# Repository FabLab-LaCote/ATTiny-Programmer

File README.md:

#ATtiny Programmer

This shield for Arduino Nano is compatible for ATtiny 45, 85, 44 and 84

Find all informations here: http://www.fablab-lacote.ch/wiki/attiny

## Material
- 3x Resistors 220 ohms 0.25W
- 3x LEDS 3mm
- 1x capacitor 10uF
- 2x 15 pins header
- 1x IC chipset 8 pins

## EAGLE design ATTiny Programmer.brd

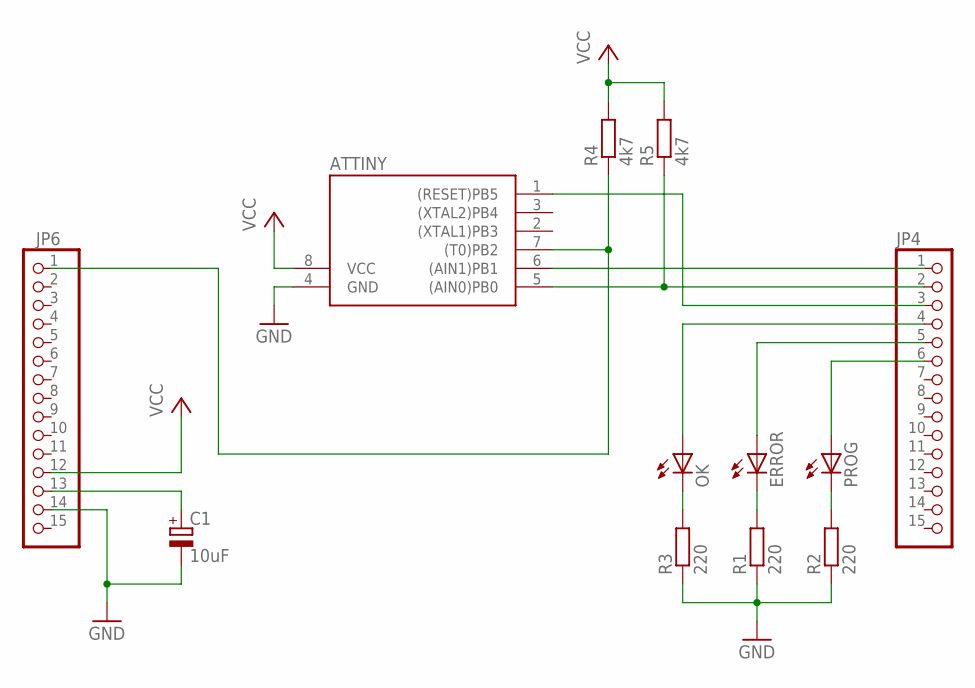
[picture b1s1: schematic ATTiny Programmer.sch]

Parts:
ATTINY: TINY10P; DIL08
C1: 10uF; E2-4
ERROR: Error; LED3MM
JP4: pinheader1; 1X15
JP6: pinheader2; 1X15
OK: Ok; LED3MM
PROG: Prog; LED3MM
R1, R2, R3: 220; 0207/7
R4, R5: 4k7; 0207/7

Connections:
GND: ATTINY.4 (GND), C1.-, JP6.14, R1.1, R2.1, R3.1
unnamed: OK.K (C), R3.2
unnamed: PROG.K (C), R2.2
unnamed: ERROR.K (C), R1.2
unnamed: C1.+, JP6.13
unnamed: JP4.4, OK.A
unnamed: ERROR.A, JP4.5
unnamed: ATTINY.1 ((RESET)PB5), JP4.3
unnamed: ATTINY.5 ((AIN0)PB0), JP4.2, R5.1
unnamed: ATTINY.6 ((AIN1)PB1), JP4.1
unnamed: ATTINY.7 ((T0)PB2), JP6.1, R4.1
unnamed: JP4.6, PROG.A
VCC: ATTINY.8 (VCC), JP6.12, R4.2, R5.2

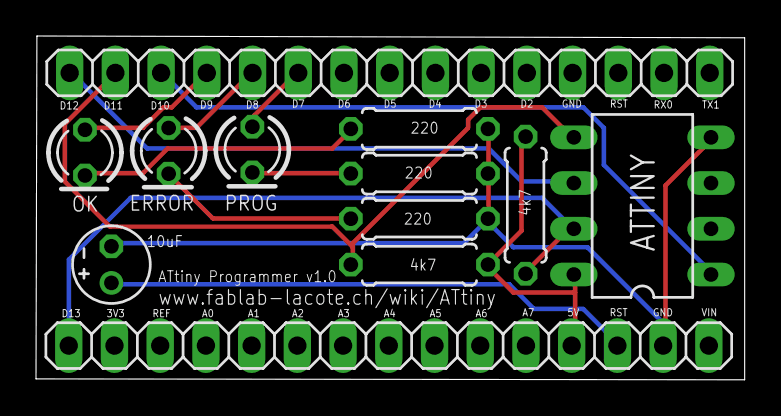
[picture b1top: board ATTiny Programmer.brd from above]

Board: 2 copper layers, 39.4 x 19.1 mm, 12 parts (0 on the bottom side), 13 nets.

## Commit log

2016-04-21 Schematics
2016-04-21 unless files
2016-04-21 attiny master
